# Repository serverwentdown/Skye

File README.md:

# Skye - your cute microcontroller

Are you looking for a flashy microcontroller as a keychain, but don't want to hang 
an Arduino? Or are you in need of a tiny microcontroller to put in your next project? 
Or, want to show off your coding skills but don't want to buy an RGB LED and 
resistors? Need somthing portable for your next VUSB hack? 

Skye is the tiny microcontroller for the casual. With a small form factor, a 
WS2812B LED and a low price, Skye is the cutest microcontroller you'll ever own. 

Features:
* WS2812B
* It's a keychain!
* Minimalistic top surface
* Breadboard-friendly headers
* Smaller than many USB sticks
* But it's a keychain!

Specifications: 
* ATtiny85
* Sized at 12.7mm by 24.4mm
* 6 IO pins
* 5V and GND pins (if you want to power it with an external power source, you can connect it with the included 5V regulator)
* Runs the [micronucleus](https://github.com/micronucleus/) bootloader! 

Hardware designs are released CC-BY-SA, credits to Digispark for the circuit design. Arduino IDE board definitions and example code are available under GPLv3, readable in `software/LICENSE`.

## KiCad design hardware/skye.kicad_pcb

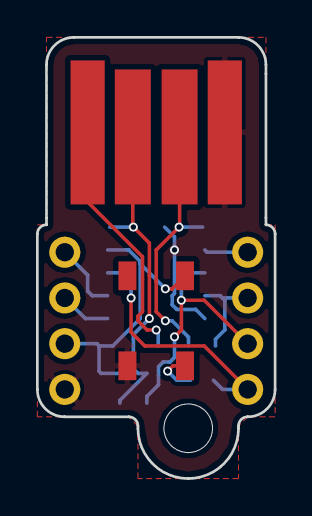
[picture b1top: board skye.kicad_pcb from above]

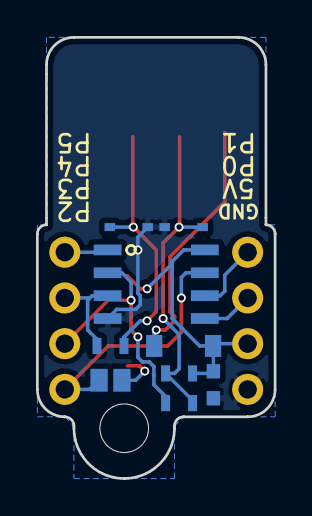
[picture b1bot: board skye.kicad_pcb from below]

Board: 2 copper layers, 13.2 x 24.5 mm, 13 parts (11 on the bottom side), 12 nets.

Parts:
C1: 1u-5u; C_0603
D1: MBR0520LT; SOD-123
D2, D3: 3V6; SOD-323
IC1: ATTINY85-20SUR; SOIC-8_3.9x4.9mm_Pitch1.27mm
JP1: JUMPER; GS2
P1, P2: IO; Pin_Header_Straight_1x04
P3: USB_A; usb-PCB
R1: 1.5k; R_0603
R2, R3: 66; R_0603
U1: WS2812; LED_WS2812B-PLCC4

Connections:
+5V: C1.1, D1.1, IC1.8, P1.2, R1.2, U1.1
GND: C1.2, D2.2, D3.2, IC1.4, P1.1, P3.4, U1.3
unnamed: D1.2, P3.1
unnamed: D2.1, P3.2, R1.1, R2.2
unnamed: D3.1, P3.3, R3.2
unnamed: IC1.1, P2.4
unnamed: IC1.2, P2.2, R2.1
unnamed: IC1.3, P2.3, R3.1
unnamed: IC1.5, P1.3
unnamed: IC1.6, P1.4
unnamed: IC1.7, JP1.1, P2.1
unnamed: JP1.2, U1.4

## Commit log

2016-06-15 Add README.md introduction
2016-06-16 Rotated 90deg
2016-06-16 Routed connections
2016-06-16 Cleanups and pinout
2016-06-16 Cleanup #2, fixes #1, adds animation
2016-06-16 Update README.md
    Can now boast it's breadboard friendly.
2016-06-16 Update README.md
    Added sizes
2016-06-17 Update README.md
    Added reference to micronucleus.
2016-06-19 Add LICENSE
2016-06-28 Rename files to Skye
2016-06-28 Added titles to docs
2016-06-28 Renamed Chloé to Skye in README
    Also added LICENSE lines.
2016-06-28 Updated gerber and PDF files, edited silkscreen
2016-06-28 Moved hardware into hardware, added software folder
2016-06-28 Added zenier diodes
2016-07-01 Updated photo, changed to static animations
2016-07-01 Updated silkscreen, removed animation
2016-07-01 Added clearence dimension
2018-08-06 Add ArduinoISP from Arduino
2018-08-06 Fix licensing and add shopping cart
